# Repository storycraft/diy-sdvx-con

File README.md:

# SDVX Controller Firmware
DIY SDVX Controller Firmware for RP235X microcontroller family.

## Key Features
- Gamepad, keyboard, mouse input methods.
- Dynamic keymapping using [Via](https://www.usevia.app/).
- Multithreaded LED control.
- Efficient cooperative multitasking architecture via async Rust([Embassy](https://embassy.dev/)).
- Official SDVX controller(EAC Mode) compatibility.

## Mode switching
- Pressing FX1 + FX2 + BT1 + Start on start changes to eac mode.
- Pressing FX1 + FX2 + BT2 + Start on start changes to kbm mode.

## Requirements
- Rust Toolchain (for development. With `thumbv8m.main-none-eabihf` target)
- picotool (for flashing the firmware)

## Flashing
To build and flash firmware, use the following command on workspace root:
```bash
cargo xtask flash --release
```

## GPIO Pinouts
0. Button1
1. Button2
2. Button3
3. Button4
4. FX Button1
5. FX Button2
6. Start Button
7. unused
8. Button1 LED Control
9. Button2 LED Control
10. Button3 LED Control
11. Button4 LED Control
12. FX Button1 LED Control
13. FX Button2 LED Control
14. Start Button LED Control
15. unused
16. unused
17. unused
18. unused
19. unused
20. unused
21. unused
22. unused
23. unused
24. unused
25. unused
26. Left knob
27. Right knob
28. unused

## Credits
* [TolLight](https://x.com/light0185): Silkscreen illustration

## License
The firmware source code is licensed under GPL-2.0.

The PCB design is licensed under CC BY-NC-ND.

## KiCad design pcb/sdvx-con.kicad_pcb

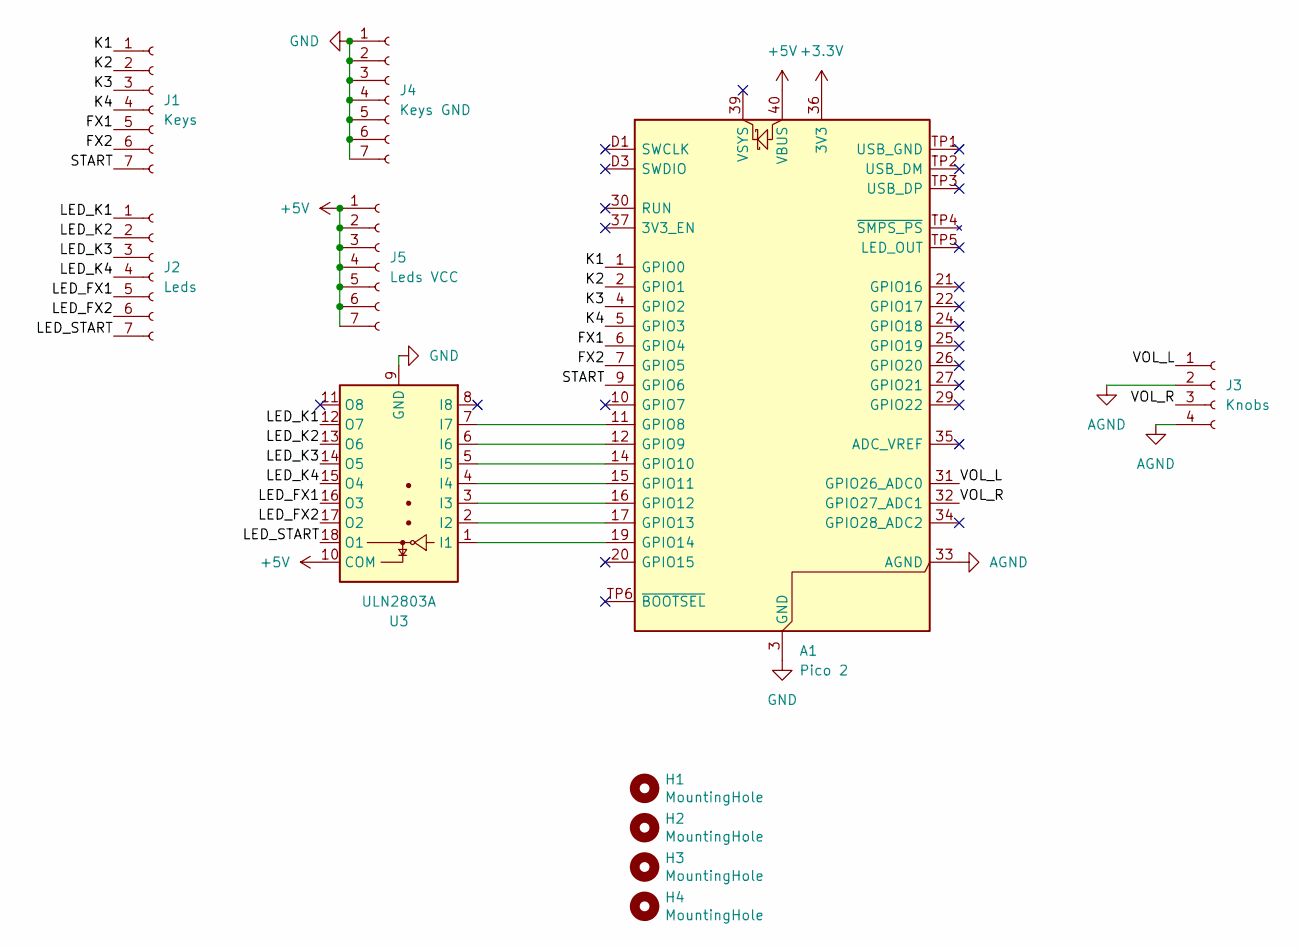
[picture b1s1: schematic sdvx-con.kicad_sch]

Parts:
A1: Pico 2; RaspberryPi_Pico_SMD_HandSolder
H1, H2, H3, H4: MountingHole; MountingHole_3.2mm_M3
J1: Keys; PinHeader_1x07_P2.54mm_Vertical
J2: Leds; PinHeader_1x07_P2.54mm_Vertical
J3: Knobs; PinHeader_1x04_P2.54mm_Vertical
J4: Keys GND; PinHeader_1x07_P2.54mm_Vertical
J5: Leds VCC; PinHeader_1x07_P2.54mm_Vertical
U3: ULN2803A; SOIC-18W_7.5x11.6mm_P1.27mm

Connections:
+3.3V: A1.36 (3V3)
+5V: A1.40 (VBUS), J5.1, J5.2, J5.3, J5.4, J5.5, J5.6, J5.7, U3.10 (COM)
/FX1: A1.6 (GPIO4), J1.5
/FX2: A1.7 (GPIO5), J1.6
/K1: A1.1 (GPIO0), J1.1
/K2: A1.2 (GPIO1), J1.2
/K3: A1.4 (GPIO2), J1.3
/K4: A1.5 (GPIO3), J1.4
/LED_FX1: J2.5, U3.16 (O3)
/LED_FX2: J2.6, U3.17 (O2)
/LED_K1: J2.1, U3.12 (O7)
/LED_K2: J2.2, U3.13 (O6)
/LED_K3: J2.3, U3.14 (O5)
/LED_K4: J2.4, U3.15 (O4)
/LED_START: J2.7, U3.18 (O1)
/START: A1.9 (GPIO6), J1.7
/VOL_L: A1.31 (GPIO26_ADC0), J3.1
/VOL_R: A1.32 (GPIO27_ADC1), J3.3
AGND: A1.33 (AGND), J3.2, J3.4
GND: A1.3 (GND), A1.8 (GND), A1.13 (GND), A1.18 (GND), A1.23 (GND), A1.28 (GND), A1.38 (GND), A1.D2 (GND), J4.1, J4.2, J4.3, J4.4, J4.5, J4.6, J4.7, U3.9 (GND)
unnamed: A1.11 (GPIO8), U3.7 (I7)
unnamed: A1.12 (GPIO9), U3.6 (I6)
unnamed: A1.14 (GPIO10), U3.5 (I5)
unnamed: A1.15 (GPIO11), U3.4 (I4)
unnamed: A1.16 (GPIO12), U3.3 (I3)
unnamed: A1.17 (GPIO13), U3.2 (I2)
unnamed: A1.19 (GPIO14), U3.1 (I1)

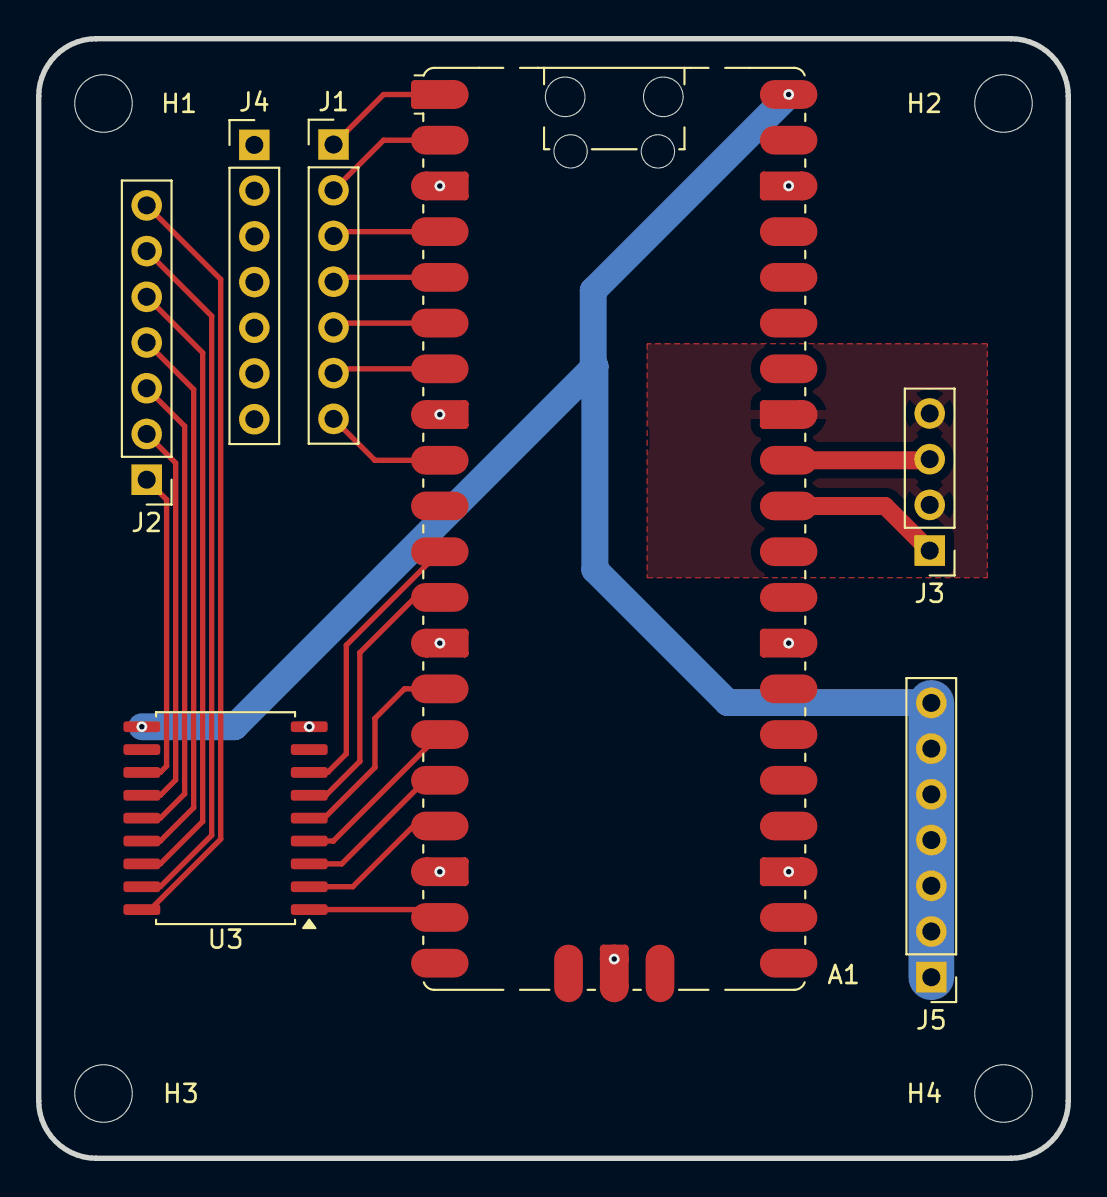
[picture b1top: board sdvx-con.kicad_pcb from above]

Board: 2 copper layers, 57.2 x 62.2 mm, 12 parts (1 on the bottom side), 26 nets.

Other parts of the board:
Github: LOGO; qr-code

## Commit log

2025-12-27 chore: logging
2025-12-27 chore: set max log level to info in release
2025-12-27 chore: remove usbd-hid-macros
2025-12-27 feat: gamepad hid descriptor
2025-12-27 chore: use 4 direction hat
2025-12-27 chore: doc
2025-12-27 chore: cleanup code
2025-12-28 revert: D-pad state to 8 states
2025-12-28 feat: setup led task
2025-12-28 feat: setup input task
2025-12-28 feat: use input, led task. Run usb as main task
2025-12-28 chore: add embassy-time
2025-12-28 feat: timestamped logging
2025-12-28 feat: add timer
2025-12-28 feat: move led task to second core
2025-12-28 feat: impl async led
2025-12-28 feat: only update if state is changed
2025-12-28 feat: update led on update
2025-12-28 fix: byte order
2025-12-28 fix: set inversion
2025-12-28 feat: knob handling
2025-12-28 chore: clippy
2025-12-28 fix: button offset
2025-12-28 fix: rotation
2025-12-28 feat: reserve flash memory for userdata
2025-12-28 feat: add qmk via hid
2025-12-28 chore: adjust via polling rate
2025-12-28 chore: adjust input max packet size
2025-12-28 feat: impl basic via commands
2025-12-28 feat: stub keycode, channel
2025-12-28 feat: impl reboot bootsel
2025-12-28 feat: disable macro
2025-12-28 feat: cleanup
2025-12-28 chore: add controller_mode stub
2025-12-28 feat: split input reader, knob state
2025-12-28 feat: cleanup input reading
2025-12-28 feat: update license
2025-12-28 feat: remove packed
2025-12-29 chore: specify explicit little endian
2025-12-29 feat: firmware version command
2025-12-29 fix: endian
2025-12-29 feat: add via logging
2025-12-29 chore: move config to usb
2025-12-29 feat: userdata io
2025-12-29 refactor: move io related functions, rename UserData to Userdata
2025-12-29 refactor: cleanup code, remove reset
2025-12-29 chore: fmt
2025-12-29 feat: split init and task
2025-12-29 chore: move usb task
2025-12-29 feat: split start phase
2025-12-29 feat: userdata task, singleton methods
2025-12-29 feat: split changes and saving
2025-12-29 feat: impl saving
2025-12-29 feat: impl config get, save
2025-12-29 feat: remove copy from Userdata
2025-12-29 chore: manual Default impl
2025-12-29 fix: io, use enum variant as signature
2025-12-29 fix: use get
2025-12-29 fix: add defmt fix
2025-12-29 feat: erase before writing
2025-12-29 feat: use custom keymap
2025-12-29 refactor: rename keys
2025-12-29 feat: impl keymap
2025-12-29 feat: DYNAMIC_KEYMAP_GET_BUFFER, DYNAMIC_KEYMAP_SET_BUFFER handling
2025-12-29 feat: impl knob keymap
2025-12-30 feat: better keymap emaulation
2025-12-30 feat: use zerocopy via cmds
2025-12-30 fix: buffer range
2025-12-30 fix: save after buffer update
2025-12-30 feat: add via.json
2025-12-30 feat: save after encoder changes
2025-12-30 feat: update max interface count
2025-12-30 fix: env value type
2025-12-30 feat: use gen_hid_descriptor macro
2025-12-30 fix: usage page
2025-12-30 feat: add inputs
2025-12-30 feat: add more states
2025-12-30 fix: increase handler count too
2025-12-30 feat: cleanup hid writers
2025-12-30 feat: fix license due to derivatived port of QMK Via
2025-12-30 chore: update README
2025-12-30 feat: use Signal for led
2025-12-30 feat: only loop on input changes
2025-12-30 feat: button debouncer
2025-12-30 feat: use ticker for consistent timing
2025-12-30 feat: debounced input
2025-12-30 fix: elapsed calc
2025-12-30 feat: use duration_since
2025-12-30 fix: temp fix duration
2025-12-31 feat: use defmt logging
2025-12-31 fix: disable defmt-rtt
2026-01-01 refactor: split each usb device into its own task
2026-01-01 feat: add set_invalid method
2026-01-01 chore: set_invalid consume
2026-01-01 chore: ViaCmd method visibility
2026-01-01 chore: add out of range handling comment
2026-01-01 feat: buffer copy range handling
2026-01-01 feat: use Cargo workspace
2026-01-01 feat: add qmk sparse keycode submodule
2026-01-01 chore: rename package to keycode-gen
2026-01-01 feat: crate specific build target
2026-01-01 chore: remove unused metadata
2026-01-01 fix: wrong direction value
2026-01-01 feat: increase sample count
2026-01-01 feat: tmp ticker
2026-01-01 fix: code
2026-01-01 fix: GamepadInputReport layout
2026-01-01 revert: ticker
2026-01-01 feat: use raw knob value for deadzoning
2026-01-01 feat: knob filter for stable input, move filters
2026-01-01 chore: knob filter comment
2026-01-01 chore: update button debouncer comment
2026-01-01 feat: reduce oversample count
2026-01-01 chore: update comment
2026-01-01 fix: add eq
2026-01-01 revert: config toml and alias
2026-01-01 feat: apply median mean filter
2026-01-01 chore: mark unreachable code
2026-01-01 chore: adjust throttle duration to be twice of threshold
2026-01-02 feat: xtask and cross comp workspace setup
2026-01-02 feat: split button, knob filters for better testing
2026-01-02 refactor: cleanup code, split button, knob reading
2026-01-02 fix: return 0 delta for ranges in threshold
2026-01-02 chore: set clockdiv
2026-01-02 chore: increase threshold value
2026-01-02 feat: qmk keycode parsing
2026-01-02 feat: impl category merging
2026-01-02 feat: add keycode crate
2026-01-02 chore: prettify build.rs output
2026-01-02 fix: key range
2026-01-02 chore: add doc only when there are non-empty label
2026-01-02 feat: split declaration and impl
2026-01-02 feat: conversion
2026-01-02 feat: default impl
2026-01-02 feat: use new keycode
2026-01-02 feat: gamepad input builder
2026-01-02 feat: split report task
2026-01-02 feat: use start end constant instead of range
2026-01-02 feat: apply custom keymap gamepad, mouse input
2026-01-02 fix: construct report even if key is not pressed
2026-01-02 feat: keyboard input
2026-01-02 chore: fmt, clippy
2026-01-03 feat: min filter for better noise filter
2026-01-03 feat: cleanup code, add via matrix state cmd
2026-01-03 feat: report input only if there are pressed button or changes
2026-02-12 chore: update knbo throttle value
2026-02-12 feat: remove media control
2026-02-12 feat: eac mode config
2026-02-12 fix: reboot
2026-02-12 feat: update via.json
2026-02-12 fix: input matrix
2026-02-12 feat: input mode hotkey
2026-02-12 feat: initial eac mode impl
    * remove KnobTurn conversion until hid report
2026-02-12 feat: eac report and hid desc
2026-02-12 fix: max packet size
2026-02-12 fix: axis type
2026-02-12 feat: update missing desc
2026-02-12 fix: report size
2026-02-13 feat: usb handler
2026-02-13 feat: hid handler, led handling
2026-02-13 fix: start
2026-02-13 chore: update doc
2026-02-13 chore: split hid, eac config
2026-02-13 fix: range to i8
2026-02-13 feat: abs, delta knob filter, fix eac mode knob
2026-02-13 chore: update README about eac
2026-03-21 feat: add pcb design and license
2026-04-30 feat: remove hid led control, use default led control
2026-05-07 chore: include mode switching method
2026-05-07 fix: typo
